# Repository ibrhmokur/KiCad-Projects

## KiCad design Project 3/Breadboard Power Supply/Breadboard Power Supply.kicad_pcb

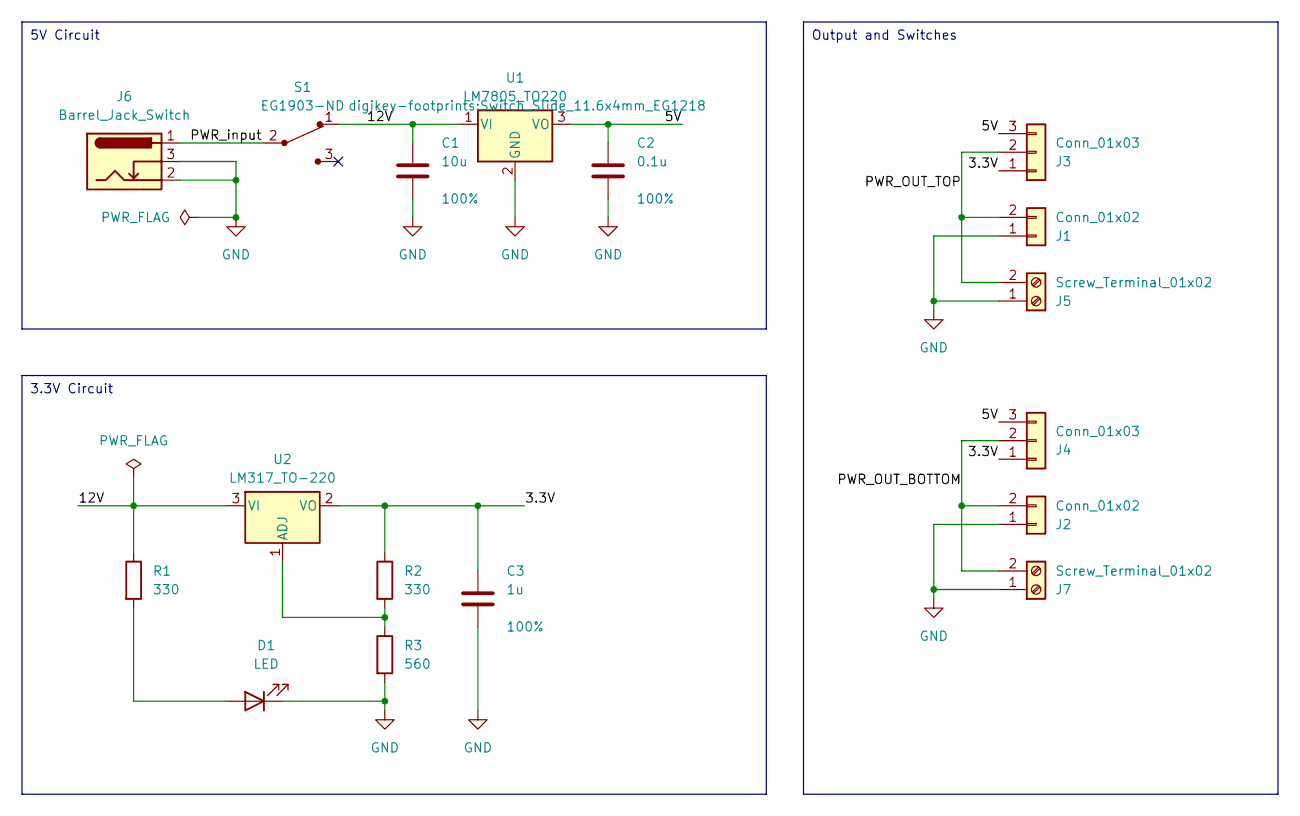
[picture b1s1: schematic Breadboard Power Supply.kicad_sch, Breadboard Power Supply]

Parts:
C1: 10u; C_Disc_D3.0mm_W1.6mm_P2.50mm; Tolerance 100%
C2: 0.1u; C_Disc_D3.0mm_W1.6mm_P2.50mm; Tolerance 100%
C3: 1u; C_Disc_D3.0mm_W1.6mm_P2.50mm; Tolerance 100%
D1: LED; LED_D5.0mm
J1, J2: Conn_01x02; PinHeader_1x02_P2.54mm_Vertical
J3, J4: Conn_01x03; PinHeader_1x03_P2.54mm_Vertical
J5, J7: Screw_Terminal_01x02; TerminalBlock_bornier-2_P5.08mm
J6: Barrel_Jack_Switch; BarrelJack_Horizontal
R1, R2: 330; R_Axial_DIN0204_L3.6mm_D1.6mm_P7.62mm_Horizontal
R3: 560; R_Axial_DIN0204_L3.6mm_D1.6mm_P7.62mm_Horizontal
S1: EG1903-ND; Switch_Slide_11.6x4mm_EG1218
U1: LM7805_TO220; TO-220-3_Vertical
U2: LM317_TO-220; TO-220-3_Vertical

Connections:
/3.3V: C3.1, J3.1, J4.1, R2.1, U2.2 (VO)
/5V: C2.1, J3.3, J4.3, U1.3 (VO)
/12V: C1.1, R1.1, S1.1, U1.1 (VI), U2.3 (VI)
/PWR_OUT_BOTTOM: J2.2, J4.2, J7.2
/PWR_OUT_TOP: J1.2, J3.2, J5.2
/PWR_input: J6.1, S1.2
GND: C1.2, C2.2, C3.2, D1.1 (K), J1.1, J2.1, J5.1, J6.2, J6.3, J7.1, R3.2, U1.2 (GND)
unnamed: D1.2 (A), R1.2
unnamed: R2.2, R3.1, U2.1 (ADJ)

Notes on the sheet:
5V Circuit
3.3V Circuit
Output and Switches

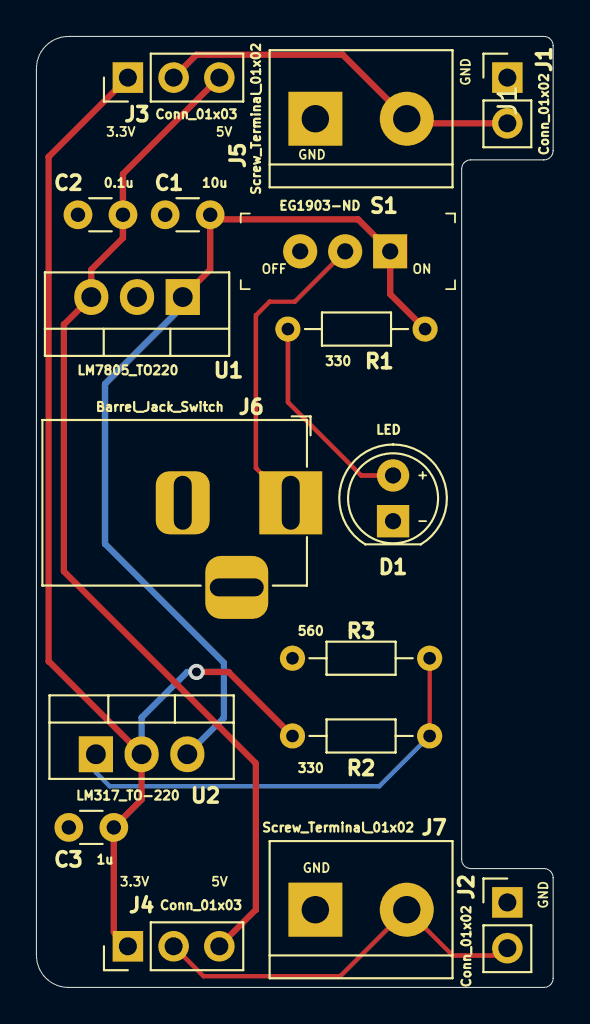
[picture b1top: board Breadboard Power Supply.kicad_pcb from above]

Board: 2 copper layers, 28.7 x 52.8 mm, 17 parts (0 on the bottom side), 9 nets.

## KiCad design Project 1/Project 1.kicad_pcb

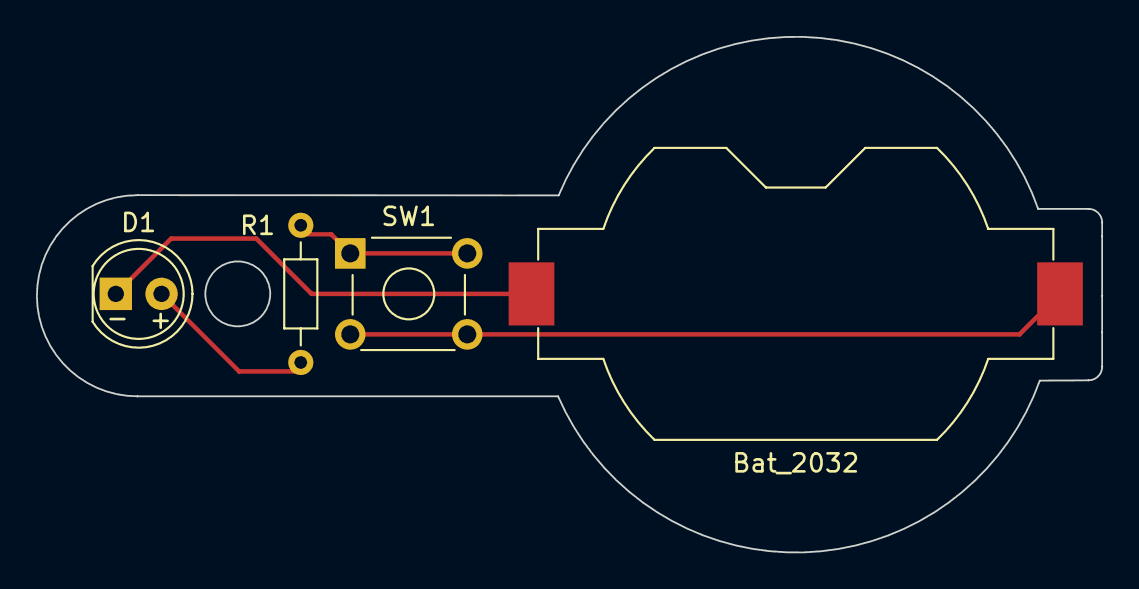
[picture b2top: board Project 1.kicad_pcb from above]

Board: 2 copper layers, 59.2 x 28.6 mm, 4 parts (0 on the bottom side), 4 nets.

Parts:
BT1: Bat_2032; BatteryHolder_Keystone_1058_1x2032
D1: LED; LED_D5.0mm
R1: R; R_Axial_DIN0204_L3.6mm_D1.6mm_P7.62mm_Horizontal
SW1: SW_DPST_x2; SW_TH_Tactile_Omron_B3F-10xx

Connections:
unnamed: BT1.1 (+), SW1.2 (B)
unnamed: BT1.2 (-), D1.1 (K)
unnamed: D1.2 (A), R1.1
unnamed: R1.2, SW1.1 (A)

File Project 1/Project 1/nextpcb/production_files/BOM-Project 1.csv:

MPN,Qty,Designator,value,manufacturer,Category,SKU,Customer Supply,Customer Remark
BK-912-TR,1,BT1,Bat_2032,Memory Protection Devices (MPD),Battery Holders,1100839847
ALED7707TR,1,D1,LED,STMicroelectronics,LED Drivers,1104102559
R1-1/2C,1,R1,R,Essentra Components,Industrial Control,-
SW3821D/U,1,SW1,SW_DPST_x2,NKK Switches,Switches,-

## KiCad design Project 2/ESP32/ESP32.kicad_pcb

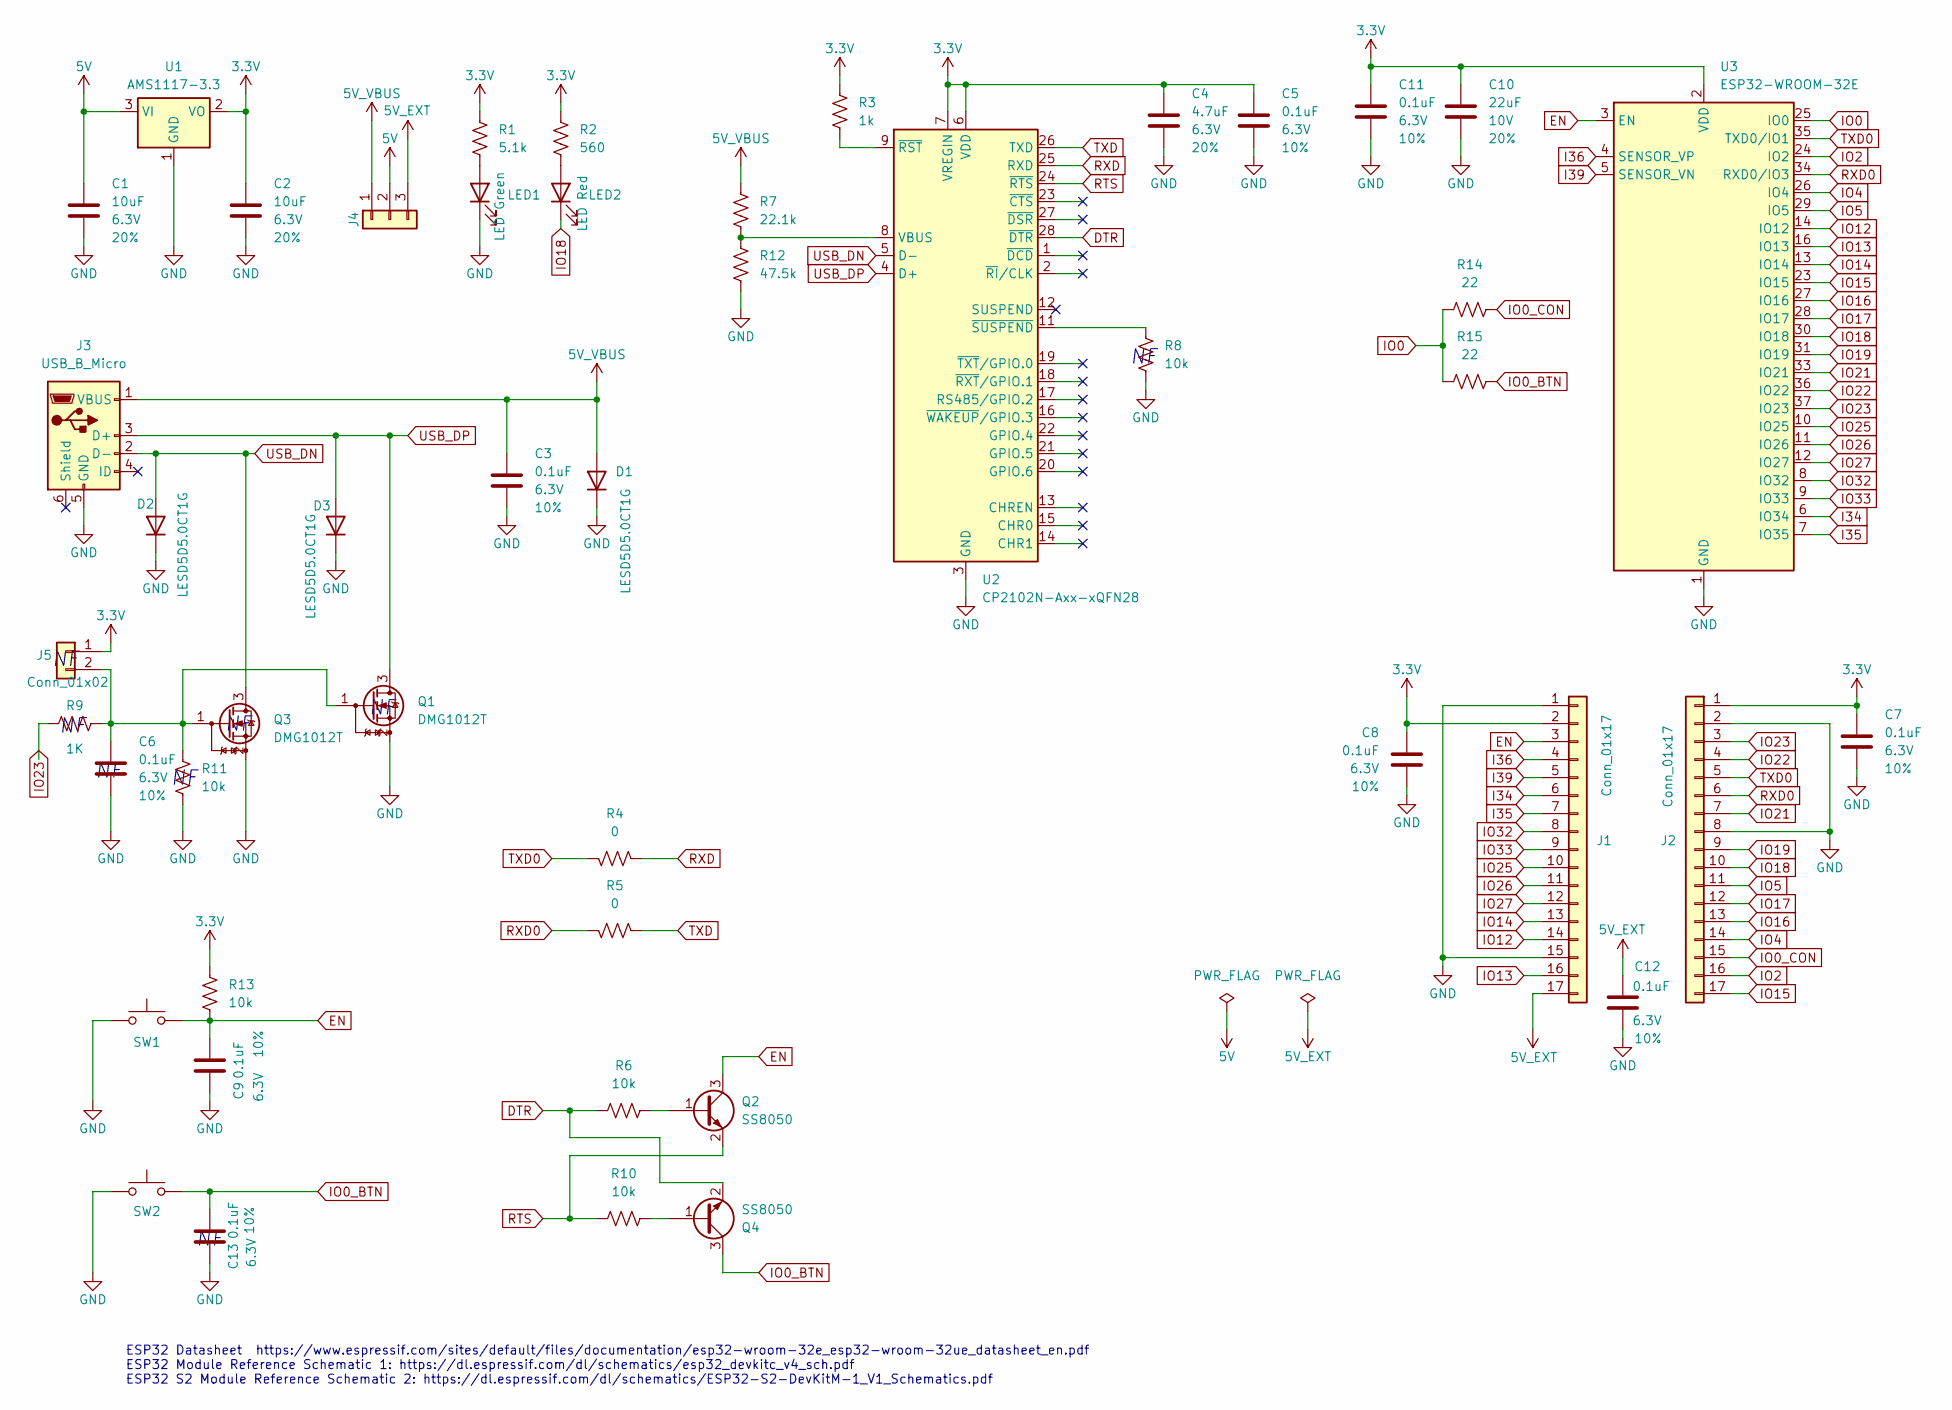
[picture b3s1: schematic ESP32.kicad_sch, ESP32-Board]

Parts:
C1, C2: 10uF; C_0402_1005Metric; Voltage 6.3V; Tolerance 20%
C3, C5, C6, C7, C8, C9, C11, C12, C13: 0.1uF; C_0402_1005Metric; Voltage 6.3V; Tolerance 10%
C4: 4.7uF; C_0402_1005Metric; Voltage 6.3V; Tolerance 20%
C10: 22uF; C_0805_2012Metric; Voltage 10V; Tolerance 20%
D1, D2, D3: LESD5D5.0CT1G; D_SOD-523
J1, J2: Conn_01x17; 1x17
J3: USB_B_Micro; USB_Micro-B_Molex-105017-0001
J4: Conn_01x03; PinHeader_1x03_P1.00mm_Vertical
J5: Conn_01x02; 1x02
LED1: LED Green; LED_0805_2012Metric
LED2: LED Red; LED_0805_2012Metric
Q1, Q3: DMG1012T; SOT-523
Q2, Q4: SS8050; SOT-23
R1: 5.1k; R_0402_1005Metric
R2: 560; R_0402_1005Metric
R3: 1k; R_0402_1005Metric
R4, R5: 0; R_0402_1005Metric
R6, R8, R10, R11, R13: 10k; R_0402_1005Metric
R7: 22.1k; R_0402_1005Metric
R9: 1K; R_0402_1005Metric
R12: 47.5k; R_0402_1005Metric
R14, R15: 22; R_0402_1005Metric
SW1, SW2: SMD_6.2x6.2mm_h7.0mm; Push_SMD_6.2x6.2mm; Mfg Part# 679-2384-2-ND
U1: AMS1117-3.3; SOT-223-3_TabPin2
U2: CP2102N-Axx-xQFN28; QFN-28-1EP_5x5mm_P0.5mm_EP3.35x3.35mm
U3: ESP32-WROOM-32E; ESP32-WROOM-32D

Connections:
3.3V: C2.1, C4.1, C5.1, C7.1, C8.1, C10.1, C11.1, J1.2, J2.1, J5.1, R1.1, R2.1, R3.1, R13.2, U1.2 (VO), U2.6 (VDD), U2.7 (VREGIN), U3.2 (VDD)
5V: C1.1, J4.2, U1.3 (VI)
5V_EXT: C12.1, J1.17, J4.3
5V_VBUS: C3.1, D1.2 (A), J3.1 (VBUS), J4.1, R7.2
DTR: Q4.2 (E), R6.2, U2.28 (~DTR)
EN: C9.2, J1.3, Q2.3 (C), R13.1, SW1.2, U3.3 (EN)
GND: C1.2, C2.2, C3.2, C4.2, C5.2, C6.2, C7.2, C8.2, C9.1, C10.2, C11.2, C12.2, C13.2, D1.1 (K), D2.1 (K), D3.1 (K), J1.1, J1.15, J2.2, J2.8, J3.5 (GND), LED1.1 (K), Q1.2 (S), Q3.2 (S), R8.2, R11.1, R12.2, SW1.1, SW2.1, U1.1 (GND), U2.3 (GND), U2.29 (GND), U3.1 (GND), U3.15 (GND), U3.38 (GND), U3.39 (GND)
I34: J1.6, U3.6 (IO34)
I35: J1.7, U3.7 (IO35)
I36: J1.4, U3.4 (SENSOR_VP)
I39: J1.5, U3.5 (SENSOR_VN)
IO0: R14.2, R15.2, U3.25 (IO0)
IO0_BTN: C13.1, Q4.3 (C), R15.1, SW2.2
IO0_CON: J2.15, R14.1
IO2: J2.16, U3.24 (IO2)
IO4: J2.14, U3.26 (IO4)
IO5: J2.11, U3.29 (IO5)
IO12: J1.14, U3.14 (IO12)
IO13: J1.16, U3.16 (IO13)
IO14: J1.13, U3.13 (IO14)
IO15: J2.17, U3.23 (IO15)
IO16: J2.13, U3.27 (IO16)
IO17: J2.12, U3.28 (IO17)
IO18: J2.10, LED2.1 (K), U3.30 (IO18)
IO19: J2.9, U3.31 (IO19)
IO21: J2.7, U3.33 (IO21)
IO22: J2.4, U3.36 (IO22)
IO23: J2.3, R9.2, U3.37 (IO23)
IO25: J1.10, U3.10 (IO25)
IO26: J1.11, U3.11 (IO26)
IO27: J1.12, U3.12 (IO27)
IO32: J1.8, U3.8 (IO32)
IO33: J1.9, U3.9 (IO33)
unnamed: C6.1, J5.2, Q1.1 (G), Q3.1 (G), R9.1, R11.2
unnamed: LED1.2 (A), R1.2
unnamed: LED2.2 (A), R2.2
unnamed: Q2.1 (B), R6.1
unnamed: Q4.1 (B), R10.1
unnamed: R7.1, R12.1, U2.8 (VBUS)
unnamed: R3.2, U2.9 (~RST)
unnamed: R8.1, U2.11 (~SUSPEND)
RTS: Q2.2 (E), R10.2, U2.24 (~RTS)
RXD: R4.2, U2.25 (RXD)
RXD0: J2.6, R5.1, U3.34 (RXD0/IO3)
TXD: R5.2, U2.26 (TXD)
TXD0: J2.5, R4.1, U3.35 (TXD0/IO1)
USB_DN: D2.2 (A), J3.2 (D-), Q3.3 (D), U2.5 (D-)
USB_DP: D3.2 (A), J3.3 (D+), Q1.3 (D), U2.4 (D+)

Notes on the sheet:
ESP32 Datasheet https://www.espressif.com/sites/default/files/documentation/esp32-wroom-32e_esp32-wroom-32ue_datasheet_en.pdf ESP32 Module Reference Schematic 1: https://dl.espressif.com/dl/schematics/esp32_devkitc_v4_sch.pdf ESP32 S2 Module Reference Schematic 2: https://dl.espressif.com/dl/schema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

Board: 2 copper layers, 47 parts (0 on the bottom side), 48 nets, no tracks yet.

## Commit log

2024-12-23 First commit. (Add KiCad projects)
2024-12-24 Schematic of Project 4 is added
2024-12-24 Files were added again.
2024-12-24 Add all projects again
2024-12-24 Add project 3 again
